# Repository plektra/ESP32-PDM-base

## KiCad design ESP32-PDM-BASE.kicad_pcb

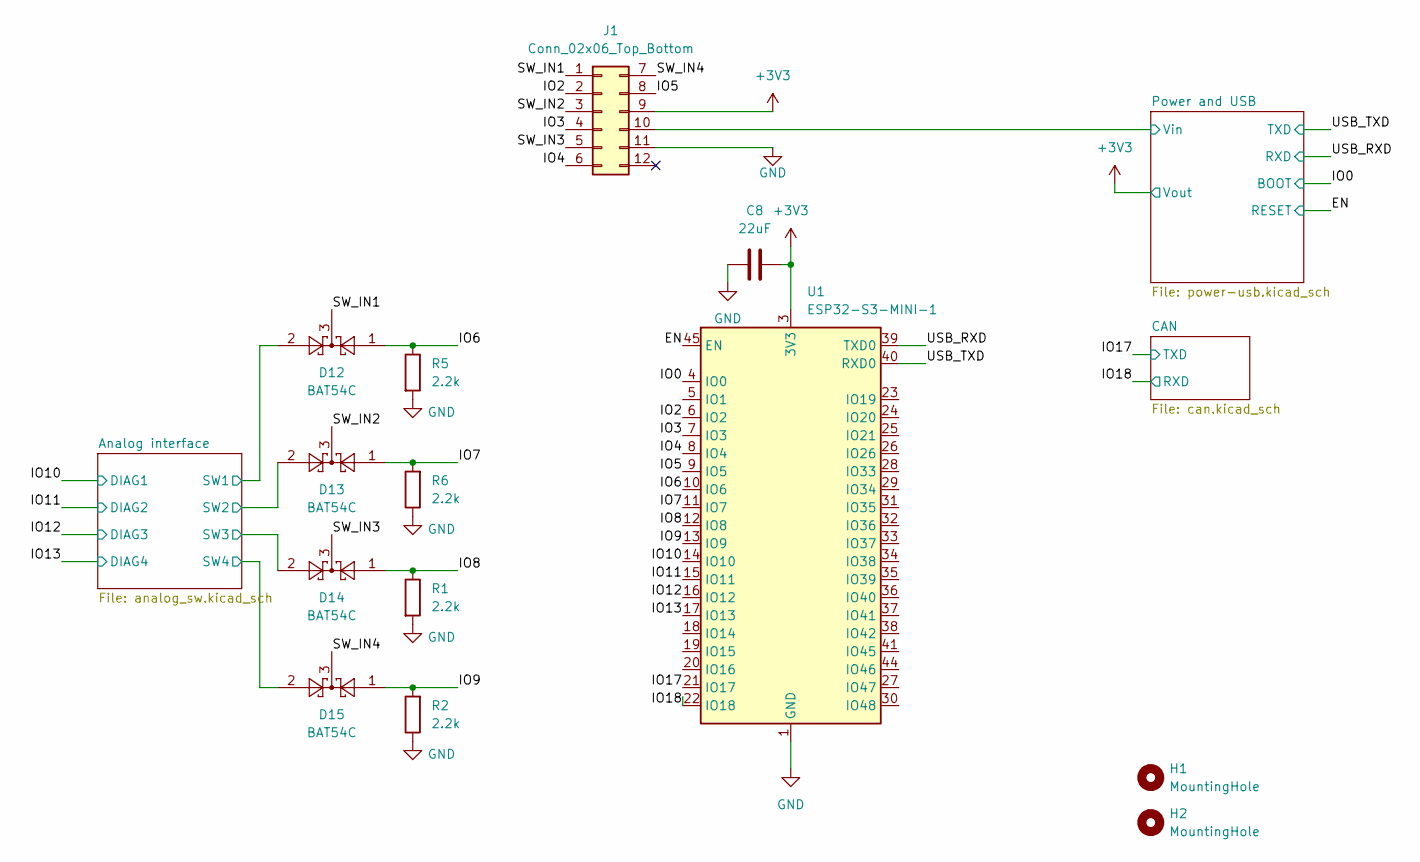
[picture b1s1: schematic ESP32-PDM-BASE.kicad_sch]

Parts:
C8: 22uF; C_0805_2012Metric
D12, D13, D14, D15: BAT54C; SOT-23
H1, H2: MountingHole
J1: Conn_02x06_Top_Bottom; PinHeader_2x06_P2.54mm_Vertical
R1, R2, R5, R6: 2.2k; R_0402_1005Metric
U1: ESP32-S3-MINI-1; ESP32-S2-MINI-1

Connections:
+3V3: C8.2, J1.9, U1.3 (3V3); also elsewhere on the board
/Analog interface/SW1: D12.2; also elsewhere on the board
/Analog interface/SW2: D13.2; also elsewhere on the board
/Analog interface/SW3: D14.2; also elsewhere on the board
/Analog interface/SW4: D15.2; also elsewhere on the board
/EN: U1.45 (EN); also elsewhere on the board
/IO0: U1.4 (IO0); also elsewhere on the board
/IO2: J1.2, U1.6 (IO2)
/IO3: J1.4, U1.7 (IO3)
/IO4: J1.6, U1.8 (IO4)
/IO5: J1.8, U1.9 (IO5)
/IO6: D12.1, R5.1, U1.10 (IO6)
/IO7: D13.1, R6.2, U1.11 (IO7)
/IO8: D14.1, R1.1, U1.12 (IO8)
/IO9: D15.1, R2.2, U1.13 (IO9)
/IO10: U1.14 (IO10); also elsewhere on the board
/IO11: U1.15 (IO11); also elsewhere on the board
/IO12: U1.16 (IO12); also elsewhere on the board
/IO13: U1.17 (IO13); also elsewhere on the board
/IO17: U1.21 (IO17); also elsewhere on the board
/IO18: U1.22 (IO18); also elsewhere on the board
/Power and USB/Vin: J1.10; also elsewhere on the board
/SW_IN1: D12.3, J1.1
/SW_IN2: D13.3, J1.3
/SW_IN3: D14.3, J1.5
/SW_IN4: D15.3, J1.7
/USB_RXD: U1.39 (TXD0); also elsewhere on the board
/USB_TXD: U1.40 (RXD0); also elsewhere on the board
GND: C8.1, J1.11, R1.2, R2.1, R5.2, R6.1, U1.1 (GND), U1.2 (GND), U1.42 (GND), U1.43 (GND), U1.46 (GND), U1.47 (GND), U1.48 (GND), U1.49 (GND), U1.50 (GND), U1.51 (GND), U1.52 (GND), U1.53 (GND), U1.54 (GND), U1.55 (GND), U1.56 (GND), U1.57 (GND), U1.58 (GND), U1.59 (GND), U1.60 (GND), U1.61 (GND), U1.62 (GND), U1.63 (GND), U1.64 (GND), U1.65 (GND); also elsewhere on the board

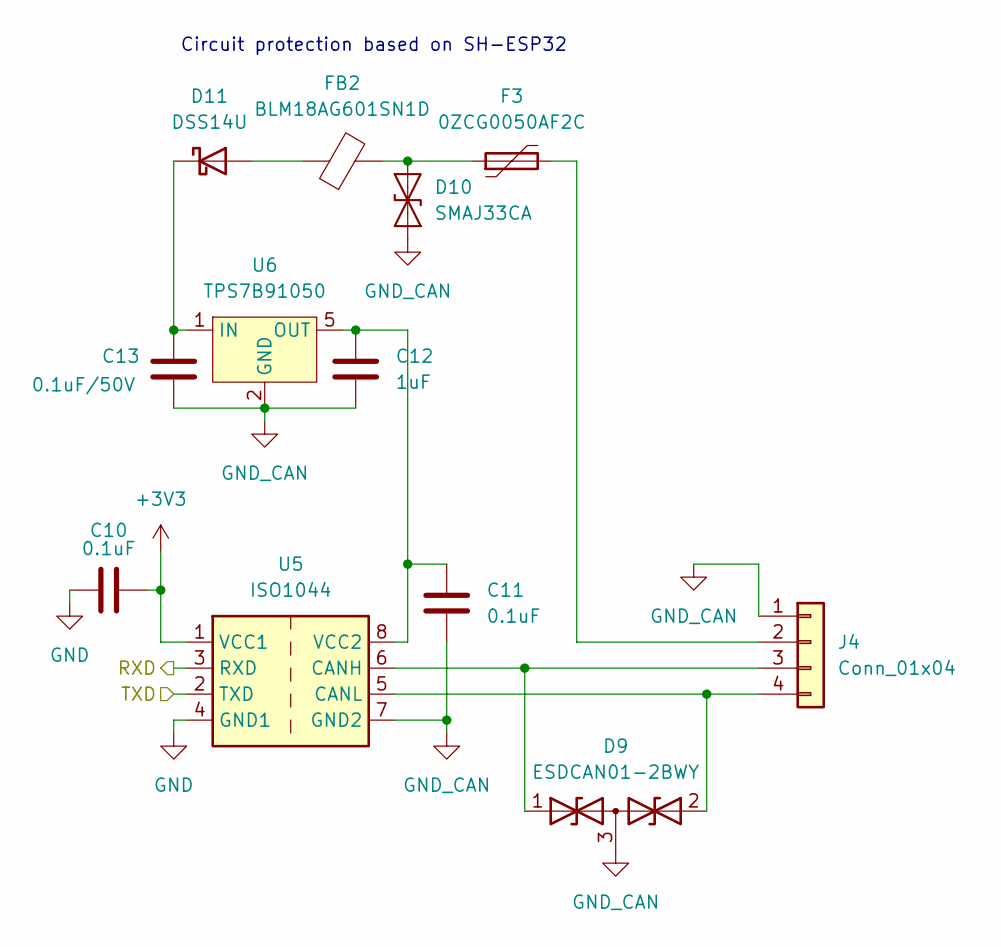
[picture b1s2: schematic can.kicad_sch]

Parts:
C10, C11: 0.1uF; C_0402_1005Metric
C12: 1uF; C_0402_1005Metric
C13: 0.1uF/50V; C_0603_1608Metric
D9: ESDCAN01-2BWY; SOT-323_SC-70
D10: SMAJ33CA; D_SMA
D11: DSS14U; D_SOD-123F
F3: 0ZCG0050AF2C
FB2: BLM18AG601SN1D; L_0603_1608Metric
J4: Conn_01x04; PhoenixContact_MCV_1,5_4-G-3.81_1x04_P3.81mm_Vertical
U5: ISO1044; SOIC-8_3.9x4.9mm_P1.27mm
U6: TPS7B91050; SOT-23-5

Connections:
+3V3: C10.2, U5.1 (VCC1); also elsewhere on the board
/IO17: U5.2 (TXD); also elsewhere on the board
/IO18: U5.3 (RXD); also elsewhere on the board
GND: C10.1, U5.4 (GND1); also elsewhere on the board
GND_CAN: C11.2, C12.2, C13.2, D9.3 (common), D10.1 (A1), J4.1, U5.7 (GND2), U6.2 (GND)
unnamed: D9.1 (A1), J4.3, U5.6 (CANH)
unnamed: D9.2 (A2), J4.4, U5.5 (CANL)
unnamed: D10.2 (A2), F3.1, FB2.2
unnamed: D11.2 (A), FB2.1
unnamed: C13.1, D11.1 (K), U6.1 (IN)
unnamed: F3.2, J4.2
unnamed: C11.1, C12.1, U5.8 (VCC2), U6.5 (OUT)

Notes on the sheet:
Circuit protection based on SH-ESP32

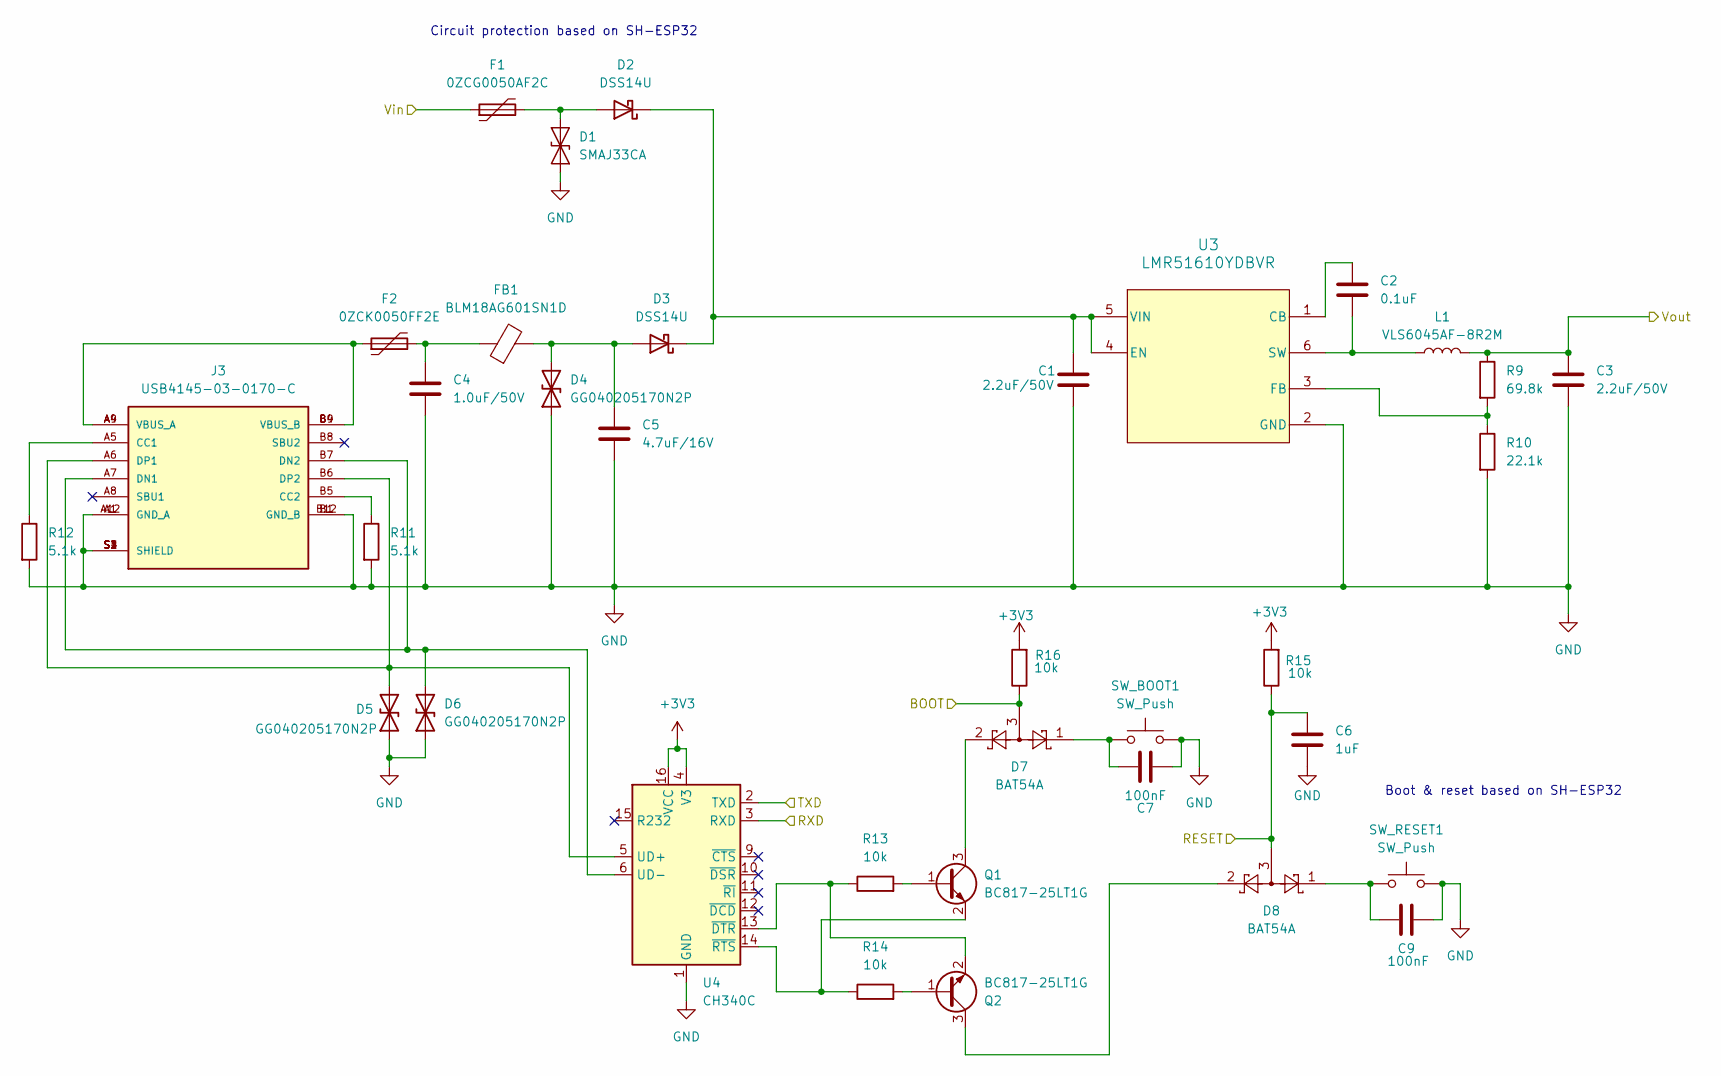
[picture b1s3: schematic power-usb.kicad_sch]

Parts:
C1, C3: 2.2uF/50V; C_0603_1608Metric
C2: 0.1uF; C_0603_1608Metric
C4: 1.0uF/50V; C_0603_1608Metric
C5: 4.7uF/16V; C_0603_1608Metric
C6: 1uF; C_0603_1608Metric
C7, C9: 100nF; C_0805_2012Metric
D1: SMAJ33CA; D_SMA
D2, D3: DSS14U; D_SOD-123F
D4, D5, D6: GG040205170N2P; D_0402_1005Metric
D7, D8: BAT54A; SOT-23
F1: 0ZCG0050AF2C
F2: 0ZCK0050FF2E; 0ZCK_BEL
FB1: BLM18AG601SN1D; L_0603_1608Metric
J3: USB4145-03-0170-C; GCT_USB4145-03-0170-C; PARTREV A2
L1: VLS6045AF-8R2M; IND_VLS6045AF-8R2M
Q1, Q2: BC817-25LT1G; SOT-23-3
R9: 69.8k; R_0603_1608Metric
R10: 22.1k; R_0603_1608Metric
R11, R12: 5.1k; R_0402_1005Metric
R13, R14, R15, R16: 10k; R_0402_1005Metric
SW_BOOT1: SW_Push; SW_SPST_PTS647_Sx38
SW_RESET1: SW_Push; SW_SPST_PTS647_Sx38
U3: LMR51610YDBVR; LMR51610
U4: CH340C; SOIC-16_3.9x9.9mm_P1.27mm

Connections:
+3V3: C3.1, L1.2, R9.1, R15.2, R16.2, U4.4 (V3), U4.16 (VCC); also elsewhere on the board
/EN: C6.1, D8.3, R15.1; also elsewhere on the board
/IO0: D7.3, R16.1; also elsewhere on the board
/Power and USB/Vin: F1.1; also elsewhere on the board
/USB_RXD: U4.3 (RXD); also elsewhere on the board
/USB_TXD: U4.2 (TXD); also elsewhere on the board
GND: C1.1, C3.2, C4.2, C5.2, C6.2, C7.1, C9.2, D1.1 (A1), D4.1 (A1), D5.1 (A1), D6.1 (A1), J3.A1 (GND_A), J3.A12 (GND_A), J3.B1 (GND_B), J3.B12 (GND_B), J3.S1 (SHIELD), J3.S2 (SHIELD), J3.S3 (SHIELD), J3.S4 (SHIELD), R10.2, R11.2, R12.2, SW_BOOT1.2, SW_RESET1.2, U3.2 (GND), U4.1 (GND); also elsewhere on the board
unnamed: C4.1, F2.2, FB1.1
unnamed: C7.2, D7.1, SW_BOOT1.1
unnamed: C9.1, D8.1, SW_RESET1.1
unnamed: D1.2 (A2), D2.2 (A), F1.2
unnamed: C1.2, D2.1 (K), D3.1 (K), U3.4 (EN), U3.5 (VIN)
unnamed: C5.1, D3.2 (A), D4.2 (A2), FB1.2
unnamed: D5.2 (A2), J3.A6 (DP1), J3.B6 (DP2), U4.5 (UD+)
unnamed: D6.2 (A2), J3.A7 (DN1), J3.B7 (DN2), U4.6 (UD-)
unnamed: F2.1, J3.A4 (VBUS_A), J3.A9 (VBUS_A), J3.B4 (VBUS_B), J3.B9 (VBUS_B)
unnamed: J3.A5 (CC1), R12.1
unnamed: J3.B5 (CC2), R11.1
unnamed: Q1.1 (B), R13.2
unnamed: D7.2, Q1.3 (C)
unnamed: Q1.2 (E), R14.1, U4.14 (~RTS)
unnamed: Q2.1 (B), R14.2
unnamed: D8.2, Q2.3 (C)
unnamed: Q2.2 (E), R13.1, U4.13 (~DTR)
unnamed: C2.1, U3.1 (CB)
unnamed: R9.2, R10.1, U3.3 (FB)
unnamed: C2.2, L1.1, U3.6 (SW)

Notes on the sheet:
Circuit protection based on SH-ESP32
Boot & reset based on SH-ESP32

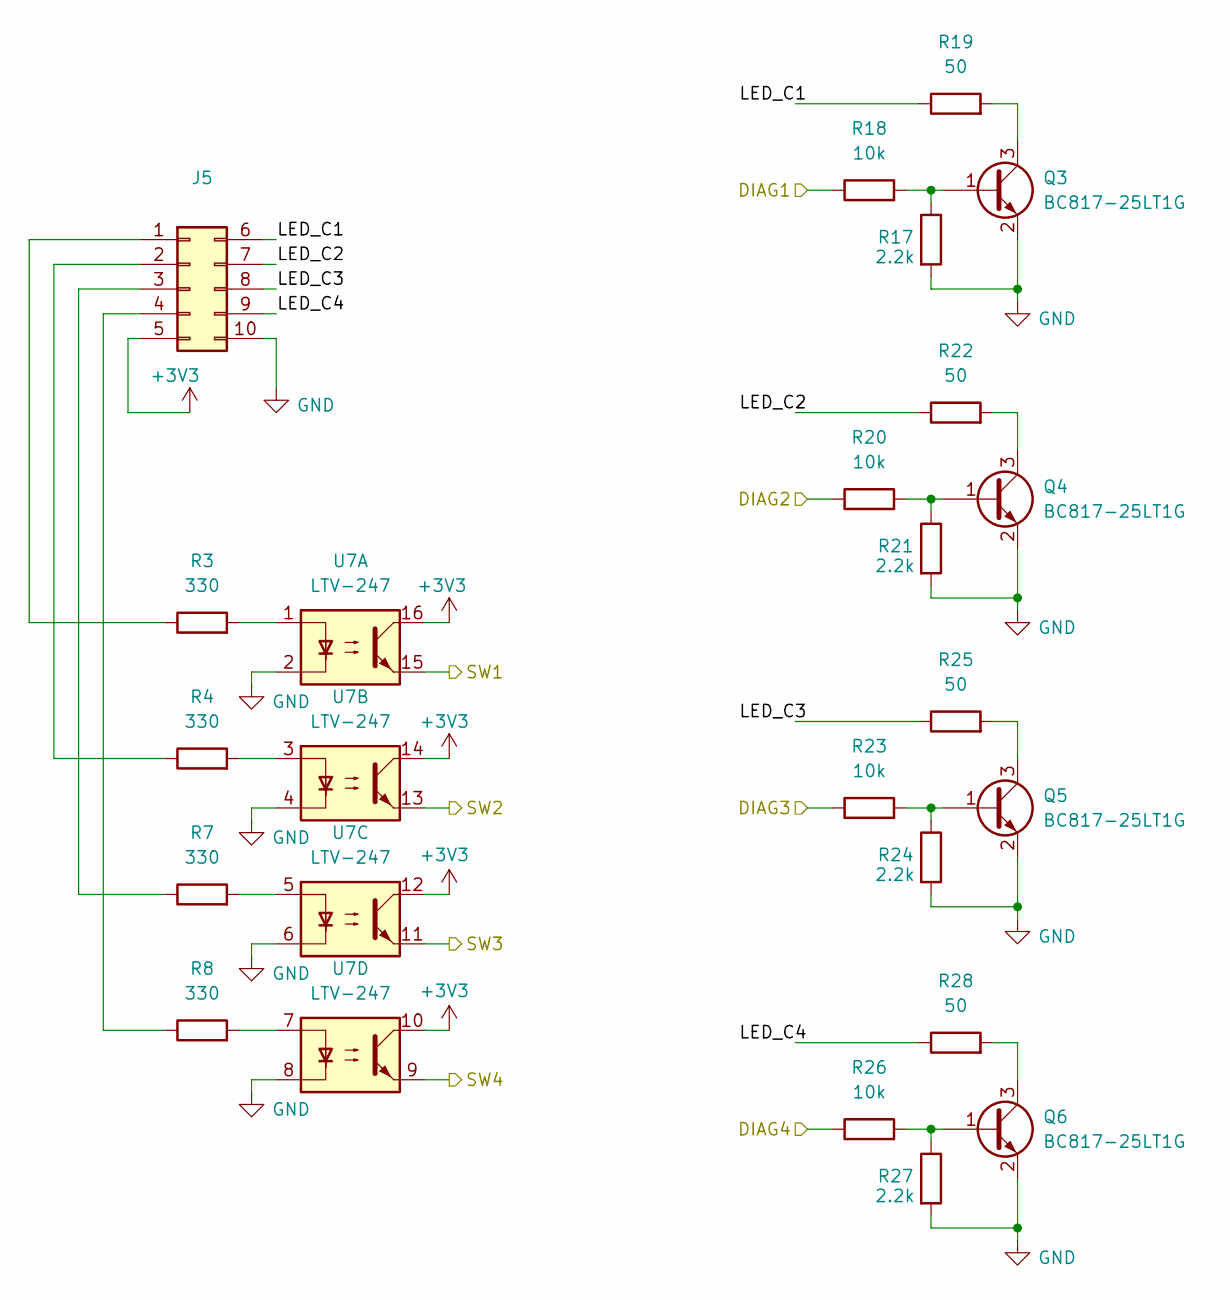
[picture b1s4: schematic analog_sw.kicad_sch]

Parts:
J5: Conn_02x05_Top_Bottom; PinHeader_2x05_P2.54mm_Vertical
Q3, Q4, Q5, Q6: BC817-25LT1G; SOT-23-3
R3, R4, R7, R8: 330; R_0603_1608Metric
R17, R21, R24, R27: 2.2k; R_0402_1005Metric
R18, R20, R23, R26: 10k; R_0402_1005Metric
R19, R22, R25, R28: 50; R_0402_1005Metric
U7: LTV-247; SOP-16_4.4x10.4mm_P1.27mm

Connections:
+3V3: J5.5, U7.10, U7.12, U7.14, U7.16; also elsewhere on the board
/Analog interface/LED_C1: J5.6, R19.1
/Analog interface/LED_C2: J5.7, R22.1
/Analog interface/LED_C3: J5.8, R25.1
/Analog interface/LED_C4: J5.9, R28.1
/Analog interface/SW1: U7.15; also elsewhere on the board
/Analog interface/SW2: U7.13; also elsewhere on the board
/Analog interface/SW3: U7.11; also elsewhere on the board
/Analog interface/SW4: U7.9; also elsewhere on the board
/IO10: R18.1; also elsewhere on the board
/IO11: R20.1; also elsewhere on the board
/IO12: R23.1; also elsewhere on the board
/IO13: R26.1; also elsewhere on the board
GND: J5.10, Q3.2 (E), Q4.2 (E), Q5.2 (E), Q6.2 (E), R17.2, R21.2, R24.2, R27.2, U7.2, U7.4, U7.6, U7.8; also elsewhere on the board
unnamed: J5.1, R3.1
unnamed: J5.2, R4.1
unnamed: J5.3, R7.1
unnamed: J5.4, R8.1
unnamed: Q3.1 (B), R17.1, R18.2
unnamed: Q3.3 (C), R19.2
unnamed: Q4.1 (B), R20.2, R21.1
unnamed: Q4.3 (C), R22.2
unnamed: Q5.1 (B), R23.2, R24.1
unnamed: Q5.3 (C), R25.2
unnamed: Q6.1 (B), R26.2, R27.1
unnamed: Q6.3 (C), R28.2
unnamed: R3.2, U7.1
unnamed: R4.2, U7.3
unnamed: R7.2, U7.5
unnamed: R8.2, U7.7

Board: 2 copper layers, 82 parts (0 on the bottom side), 77 nets, no tracks yet.

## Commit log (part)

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2025-01-17 initial schematic draft
